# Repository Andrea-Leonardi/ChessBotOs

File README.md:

# ChessBotOs

**End-to-end autonomous physical chess-playing robot** combining a custom 3D-printed **5-bar parallel SCARA manipulator**, **deep-learning computer vision (ResNet-18 + ArUco)**, **Stockfish chess engine**, **distributed ESP32 firmware**, and a **custom 2-layer KiCad mainboard PCB**.

> **Work in Progress:** Core subsystems (3D-printed SCARA hardware, inverse kinematics firmware, ArUco + ResNet-18 vision pipeline, and custom KiCad mainboard PCB) are built and tested; final PCB assembly and full end-to-end game orchestration are currently under active development.

---

## Highlights

- **5-Bar Parallel SCARA Kinematics:** Analytical inverse kinematics (`a = 183 mm`, `b = 230 mm`, `16T:100T` belt reduction) ported from Python (`IK.py`) to real-time ESP32 C++ (`scara_ik.ino`) with trapezoidal acceleration ramps and **~1.6 mm RMS positional accuracy** calibrated across 35 measured board points.
- **2-Stage Computer Vision Pipeline:** Overhead **ESP32-S3 + OV5640** autofocus camera stream with 1:1 hardware crop, **ArUco homography** board warping (`800×800` → 64 cells), and dual **PyTorch ResNet-18** models (3-class occupancy/color + 13-class full piece classification) with Class Activation Map (CAM) interpretability.
- **Custom 2-Layer Mainboard PCB:** Designed from scratch in **KiCad 10.0** (`100 × 100 mm`, **0 DRC errors**, **0 unconnected pads**), integrating an ESP32 38-pin controller, 3× **TMC2209** stepper drivers, triple **MP1584EN** buck rails (5V logic + 6V 25 kg gripper servo + low-profile 10–12V blower fan under ESP32), NC hardware E-Stop cutting motor power only (`VMOT_24V`), 5A fuse, and unified JST-XH connectors.
- **3D-Printed Mechanics & Clock Console:** Full PETG + 2020 aluminum extrusion robot CAD (`ChessBot_checkpoint_4.blend`) and a dedicated touchscreen **Chess Clock Console** (`ChessBot_ClockConsole.blend`) housing an ESP32-S3 4.0" IPS capacitive display and a mechanical MX top switch.

---

## Visual Showcase

<table>
  <tr>
    <td align="center" width="52%">
      
      <br />
      <sub><b>Custom 2-Layer Mainboard PCB v1.3</b> (100×100 mm, KiCad 10.0 — 3× TMC2209, ESP32, 3× MP1584EN, E-Stop)</sub>
    </td>
    <td align="center" width="48%">
      
      <br />
      <sub><b>ResNet-18 Piece Classifier</b> — Conv1 feature maps & Layer4 Class Activation Maps across piece classes</sub>
    </td>
  </tr>
</table>

---

## System Architecture

```mermaid
flowchart LR
    subgraph HOST["Host PC - Python / PyTorch / Stockfish"]
        CV["ArUco Warp + ResNet-18 (3-class & 13-class)"]
        ENG["Stockfish Engine & Game Orchestrator"]
        CV --> ENG
    end

    subgraph CAM["Overhead Vision Node"]
        ESP_CAM["ESP32-S3 + OV5640 (1:1 Square Stream + AF)"]
    end

    subgraph MOTION["Mainboard PCB v1.3 (24V / 12V / 6V / 5V)"]
        ESP_MOT["ESP32 38-pin - 5-Bar SCARA IK + Z-Axis"]
        DRV["3x TMC2209 + NEMA 17 + 25 kg Gripper Servo"]
        ESP_MOT --> DRV
    end

    subgraph HMI["Clock Console (3D Printed)"]
        CLK["ESP32-S3 4.0-inch IPS Touch + MX Button"]
    end

    ESP_CAM -->|HTTP / Wi-Fi| CV
    ENG -->|Move Commands| ESP_MOT
    ENG <-->|Clock & UX State| CLK
```

---

## Repository Structure

```text
ChessBotOs/
├── README.md
├── .gitignore
├── 3Dmodel/                                    # Blender CAD models
│   ├── ChessBot_checkpoint_4.blend             # Full 5-bar SCARA robot assembly (2020 frame + PETG parts)
│   └── ChessBot_ClockConsole.blend             # 3D-printable 4.0" IPS touch clock console + MX switch
├── hardware/
│   └── mainboard_pcb/                          # Custom 2-layer KiCad 10.0 Mainboard v1.3 (100x100 mm)
│       ├── Motherboard_chessbot.kicad_pro
│       ├── Motherboard_chessbot.kicad_sch      # Full schematic (0 ERC errors)
│       ├── Motherboard_chessbot.kicad_pcb      # Routed 2-layer PCB (0 DRC errors, solid B.Cu GND plane)
│       ├── ChessBot_Local.pretty/              # Custom STEP-verified MP1584EN footprint
│       ├── gerbers/                            # Production-ready Gerber + Excellon drill ZIP
│       └── ChessBot_Mainboard_v1.3_PrintCheck_1to1.pdf
├── docs/                                       # Engineering specs, BOM & hardware guides (Italian)
│   ├── riassunto_progetto_chessbot.md          # Complete project & mechatronics overview
│   ├── specifiche_funzionali_chessbot.md       # Functional specs, UX flows & Fair Clock logic
│   ├── bom_componenti_chessbot.md              # Bill of Materials aligned with CAD & PCB
│   ├── guida_pcb_kicad_chessbot.md             # PCB design & assembly guide
│   └── images/                                 # PCB 3D renders
└── test/                                       # Prototype modules & validation tools
    ├── InverseKinematic/
    │   └── IK.py                               # Analytical 5-bar parallel SCARA inverse kinematics
    ├── scara_ik/
    │   └── scara_ik.ino                        # ESP32 C++ IK firmware + serial CLI (a1..h8, z±mm, home)
    ├── stepper/
    │   └── stepper.ino                         # Stepper & microstepping bring-up test
    ├── pinzaInput/                             # Gripper servo actuation test
    ├── esp32_cam_stream/                       # ESP32-S3 (N16R8 + OV5640) web stream + autofocus firmware
    ├── aruco_markers/                          # ArUco marker generator & 800x800 perspective warp
    ├── dataset_tools/                          # Capture, 3/13-class labeling, smart collection & label review
    ├── resnet18/                               # PyTorch ResNet-18 training, live inference & CAM visualizations
    └── stockfish/                              # Stockfish engine integration test
```

---

## Subsystems & Quick Start

### 1. 5-Bar SCARA Kinematics & Motion Control (`test/InverseKinematic`, `test/scara_ik`)
- **Python prototype (`test/InverseKinematic/IK.py`):** Solves left/right shoulder angles `(θ_L, θ_R)` for any `(x, y)` coordinate or chess square (`a1`–`h8`), `home`, and `cemetery` discard zone.
- **ESP32 firmware (`test/scara_ik/scara_ik.ino`):** Real-time coordinated L/R + Z-axis (`T8×8`, `1:3` reduction) motion with trapezoidal velocity ramps and an interactive `115200` baud serial monitor:
  - Squares: `a1` .. `h8` (e.g. `e4`, `a8`)
  - Special targets: `home`, `cemetery`, direct `x,y` coordinates
  - Z-axis: relative `z+10` / `z-10` or absolute `z0` / `z20`
  - Telemetry: `pos` or `?`

### 2. ESP32-S3 Overhead Camera (`test/esp32_cam_stream`)
Firmware for **Goouuu ESP32-S3-N16R8** with **OV5640** sensor:
- Copy `credentials.example.h` → `credentials.h` (git-ignored) and set your Wi-Fi SSID/password. Falls back automatically to the `ESP32S3-CAM` access point (`192.168.4.1`).
- Hardware-cropped **1:1 square resolutions** (`1500×1500`, `1024×1024`, `800×800`) and OV5640 VCM autofocus support (`ESP32_OV5640_AF`).

### 3. ArUco Calibration & Dataset Pipeline (`test/aruco_markers`, `test/dataset_tools`)
Recommended Python environment (`conda activate chess_bot` with `opencv-python`, `numpy`, `torch`, `torchvision`, `pillow`):
```powershell
# 1. Verify ArUco perspective warp (800x800 chessboard grid)
python test/aruco_markers/MakerIdentification.py

# 2. Capture 64 cells (100x100 px) per shot (SPACE to capture, Q to quit)
python test/dataset_tools/DatasetCollector.py

# 3. Label 3-class (occupancy/color) or 13-class (piece types)
python test/dataset_tools/DatasetLabeler.py
python test/dataset_tools/PieceLabeler.py
```
Additional active-learning helpers: `SmartPieceCollector.py` (auto-filters empty squares with the 3-class model), `TargetedPieceCollector.py` (single-piece capture), and `ReviewLabels.py` (error/imbalance auditing).

### 4. ResNet-18 Piece Recognition (`test/resnet18`)
```powershell
# Train on CUDA (3-class and 13-class)
python test/resnet18/train_resnet18.py
python test/resnet18/train_resnet18_pieces.py

# Live camera inference
python test/resnet18/infer_live.py
python test/resnet18/infer_live_pieces.py

# Generate Conv1..Layer4 activation & CAM visualizations
python test/resnet18/visualize_resnet_layers.py
```

### 5. Custom Mainboard PCB (`hardware/mainboard_pcb`)
- **Board:** `100 × 100 mm`, 2 layers, 1 oz Cu, THT + socketed modules (production-ready for JLCPCB / PCBWay).
- **Power rails:** 24V input → 5A fuse (`F1`) → Main Switch (`J18`) → NC E-Stop (`J2`, cuts `VMOT_24V` only so logic stays alive) + triple `MP1584EN` buck converters (`5.0 V` logic/camera/clock, `6.0 V` gripper servo, `10–12 V` low-profile radial blower under ESP32).
- **Manufacturing package:** Ready-to-upload Gerber + Excellon drill archive in [`hardware/mainboard_pcb/gerbers/`](hardware/mainboard_pcb/gerbers/ChessBot_Mainboard_v1.3_PCBWay.zip) and a 1:1 A4 paper fit-check PDF in [`hardware/mainboard_pcb/`](hardware/mainboard_pcb/ChessBot_Mainboard_v1.3_PrintCheck_1to1.pdf).

---

## Project Status & Roadmap

- [x] 3D-printed 5-bar parallel SCARA mechanical design & working physical prototype
- [x] Analytical inverse kinematics (Python & ESP32 C++) calibrated to ~1.6 mm RMS
- [x] ESP32-S3 OV5640 streaming + ArUco homography board extraction
- [x] Custom dataset pipeline + trained 3-class & 13-class ResNet-18 models with CAM visualizations
- [x] Functional specifications, BOM, and 3D-printable 4.0" IPS Clock Console CAD
- [x] Custom 2-layer KiCad 10.0 Mainboard PCB (0 ERC/DRC errors, Gerbers ready for fabrication)
- [ ] PCB assembly & hardware bring-up with TMC2209 silent drivers + endstop homing
- [ ] Unified game orchestrator (`ChessBotOs` host + Stockfish + Fair Clock + auto-setup)
- [ ] ESP32-S3 4.0" LVGL Clock Console UI & Wi-Fi telemetry

---

## Excluded from Git (`.gitignore`)

- `credentials.h` and local secrets
- `datasets/` (raw captured board images and CSV labels)
- `stockfish-windows-x86-64-universal/` (local Stockfish binary > 100 MB)
- KiCad / Blender lockfiles and auto-backups

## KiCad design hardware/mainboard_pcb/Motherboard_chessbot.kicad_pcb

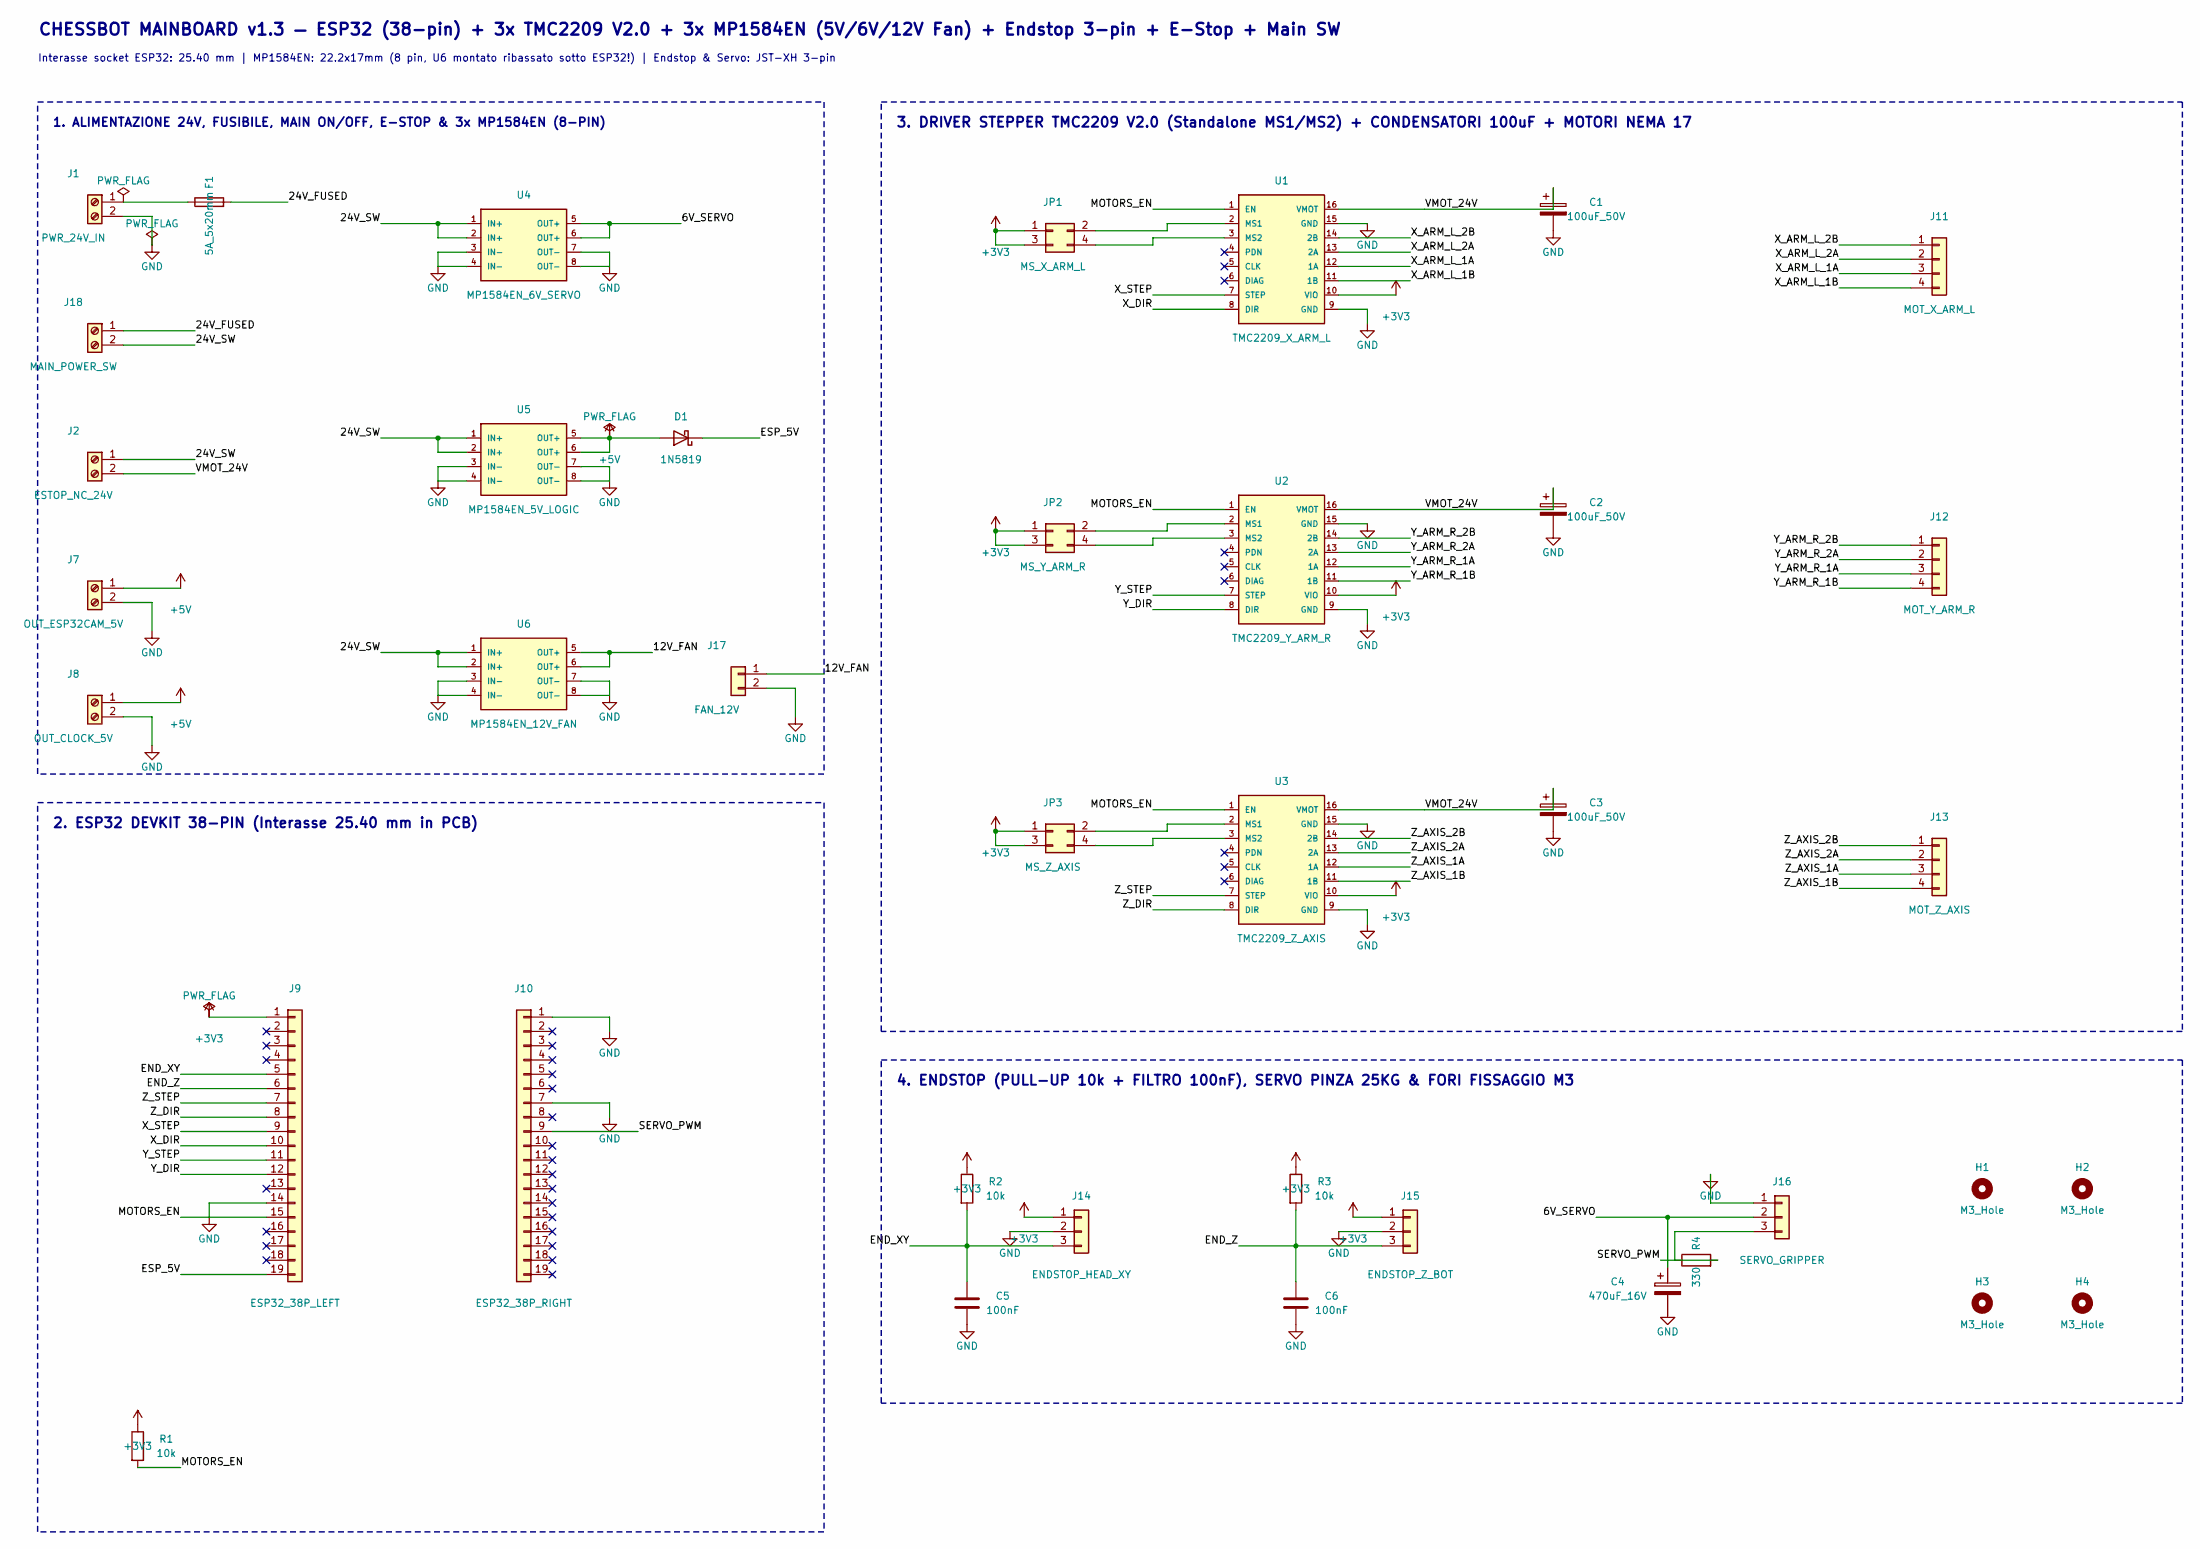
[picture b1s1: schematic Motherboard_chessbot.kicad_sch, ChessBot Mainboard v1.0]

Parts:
C1, C2, C3: 100uF_50V; CP_Radial_D8.0mm_P3.50mm
C4: 470uF_16V; CP_Radial_D8.0mm_P3.50mm
C5, C6: 100nF; C_Disc_D5.0mm_W2.5mm_P5.00mm
D1: 1N5819; D_DO-41_SOD81_P10.16mm_Horizontal
F1: 5A_5x20mm; Fuseholder_Cylinder-5x20mm_Stelvio-Kontek_PTF78_Horizontal_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
H1, H2, H3, H4: M3_Hole; MountingHole_3.2mm_M3
J1: PWR_24V_IN; TerminalBlock_Phoenix_MKDS-1,5-2-5.08_1x02_P5.08mm_Horizont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
J2: ESTOP_NC_24V; TerminalBlock_Phoenix_MKDS-1,5-2-5.08_1x02_P5.08mm_Horizont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
J7: OUT_ESP32CAM_5V; TerminalBlock_Phoenix_MKDS-1,5-2-5.08_1x02_P5.08mm_Horizont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
J8: OUT_CLOCK_5V; TerminalBlock_Phoenix_MKDS-1,5-2-5.08_1x02_P5.08mm_Horizont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
J9: ESP32_38P_LEFT; PinSocket_1x19_P2.54mm_Vertical
J10: ESP32_38P_RIGHT; PinSocket_1x19_P2.54mm_Vertical
J11: MOT_X_ARM_L; JST_XH_B4B-XH-A_1x04_P2.50mm_Vertical
J12: MOT_Y_ARM_R; JST_XH_B4B-XH-A_1x04_P2.50mm_Vertical
J13: MOT_Z_AXIS; JST_XH_B4B-XH-A_1x04_P2.50mm_Vertical
J14: ENDSTOP_HEAD_XY; JST_XH_B3B-XH-A_1x03_P2.50mm_Vertical
J15: ENDSTOP_Z_BOT; JST_XH_B3B-XH-A_1x03_P2.50mm_Vertical
J16: SERVO_GRIPPER; JST_XH_B3B-XH-A_1x03_P2.50mm_Vertical
J17: FAN_12V; JST_XH_B2B-XH-A_1x02_P2.50mm_Vertical
J18: MAIN_POWER_SW; TerminalBlock_Phoenix_MKDS-1,5-2-5.08_1x02_P5.08mm_Horizont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
JP1: MS_X_ARM_L; PinHeader_2x02_P2.54mm_Vertical
JP2: MS_Y_ARM_R; PinHeader_2x02_P2.54mm_Vertical
JP3: MS_Z_AXIS; PinHeader_2x02_P2.54mm_Vertical
R1, R2, R3: 10k; R_Axial_DIN0207_L6.3mm_D2.5mm_P10.16mm_Horizontal
R4: 330; R_Axial_DIN0207_L6.3mm_D2.5mm_P10.16mm_Horizontal
U1: TMC2209_X_ARM_L; Pololu_Breakout-16_15.2x20.3mm
U2: TMC2209_Y_ARM_R; Pololu_Breakout-16_15.2x20.3mm
U3: TMC2209_Z_AXIS; Pololu_Breakout-16_15.2x20.3mm
U4: MP1584EN_6V_SERVO; MP1584EN_22.2x17mm
U5: MP1584EN_5V_LOGIC; MP1584EN_22.2x17mm
U6: MP1584EN_12V_FAN; MP1584EN_22.2x17mm

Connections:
+3V3: J9.1, J14.1, J15.1, JP1.1, JP1.3, JP2.1, JP2.3, JP3.1, JP3.3, R1.1, R2.1, R3.1, U1.10 (VIO), U2.10 (VIO), U3.10 (VIO)
+5V: D1.2 (A), J7.1, J8.1, U5.5 (OUT+), U5.6 (OUT+)
/6V_SERVO: C4.1, J16.2, U4.5 (OUT+), U4.6 (OUT+)
/12V_FAN: J17.1, U6.5 (OUT+), U6.6 (OUT+)
/24V_FUSED: F1.2, J18.1
/24V_SW: J2.1, J18.2, U4.1 (IN+), U4.2 (IN+), U5.1 (IN+), U5.2 (IN+), U6.1 (IN+), U6.2 (IN+)
/END_XY: C5.1, J9.5, J14.3, R2.2
/END_Z: C6.1, J9.6, J15.3, R3.2
/ESP_5V: D1.1 (K), J9.19
/SERVO_PWM: J10.9, R4.2
/VMOT_24V: C1.1, C2.1, C3.1, J2.2, U1.16 (VMOT), U2.16 (VMOT), U3.16 (VMOT)
/X_ARM_L_1A: J11.3, U1.12 (1A)
/X_ARM_L_1B: J11.4, U1.11 (1B)
/X_ARM_L_2A: J11.2, U1.13 (2A)
/X_ARM_L_2B: J11.1, U1.14 (2B)
/X_DIR: J9.10, U1.8 (DIR)
/X_STEP: J9.9, U1.7 (STEP)
/Y_ARM_R_1A: J12.3, U2.12 (1A)
/Y_ARM_R_1B: J12.4, U2.11 (1B)
/Y_ARM_R_2A: J12.2, U2.13 (2A)
/Y_ARM_R_2B: J12.1, U2.14 (2B)
/Y_DIR: J9.12, U2.8 (DIR)
/Y_STEP: J9.11, U2.7 (STEP)
/Z_AXIS_1A: J13.3, U3.12 (1A)
/Z_AXIS_1B: J13.4, U3.11 (1B)
/Z_AXIS_2A: J13.2, U3.13 (2A)
/Z_AXIS_2B: J13.1, U3.14 (2B)
/Z_DIR: J9.8, U3.8 (DIR)
/Z_STEP: J9.7, U3.7 (STEP)
unnamed: F1.1, J1.1
unnamed: J16.3, R4.1
unnamed: JP1.2, U1.2 (MS1)
unnamed: JP1.4, U1.3 (MS2)
unnamed: JP2.2, U2.2 (MS1)
unnamed: JP2.4, U2.3 (MS2)
unnamed: JP3.2, U3.2 (MS1)
unnamed: JP3.4, U3.3 (MS2)

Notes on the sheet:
CHESSBOT MAINBOARD v1.3 — ESP32 (38-pin) + 3x TMC2209 V2.0 + 3x MP1584EN (5V/6V/12V Fan) + Endstop 3-pin + E-Stop + Main SW
Interasse socket ESP32: 25.40 mm | MP1584EN: 22.2x17mm (8 pin, U6 montato ribassato sotto ESP32!) | Endstop & Servo: JST-XH 3-pin
1. ALIMENTAZIONE 24V, FUSIBILE, MAIN ON/OFF, E-STOP & 3x MP1584EN (8-PIN)
2. ESP32 DEVKIT 38-PIN (Interasse 25.40 mm in PCB)
3. DRIVER STEPPER TMC2209 V2.0 (Standalone MS1/MS2) + CONDENSATORI 100uF + MOTORI NEMA 17
4. ENDSTOP (PULL-UP 10k + FILTRO 100nF), SERVO PINZA 25KG & FORI FISSAGGIO M3

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
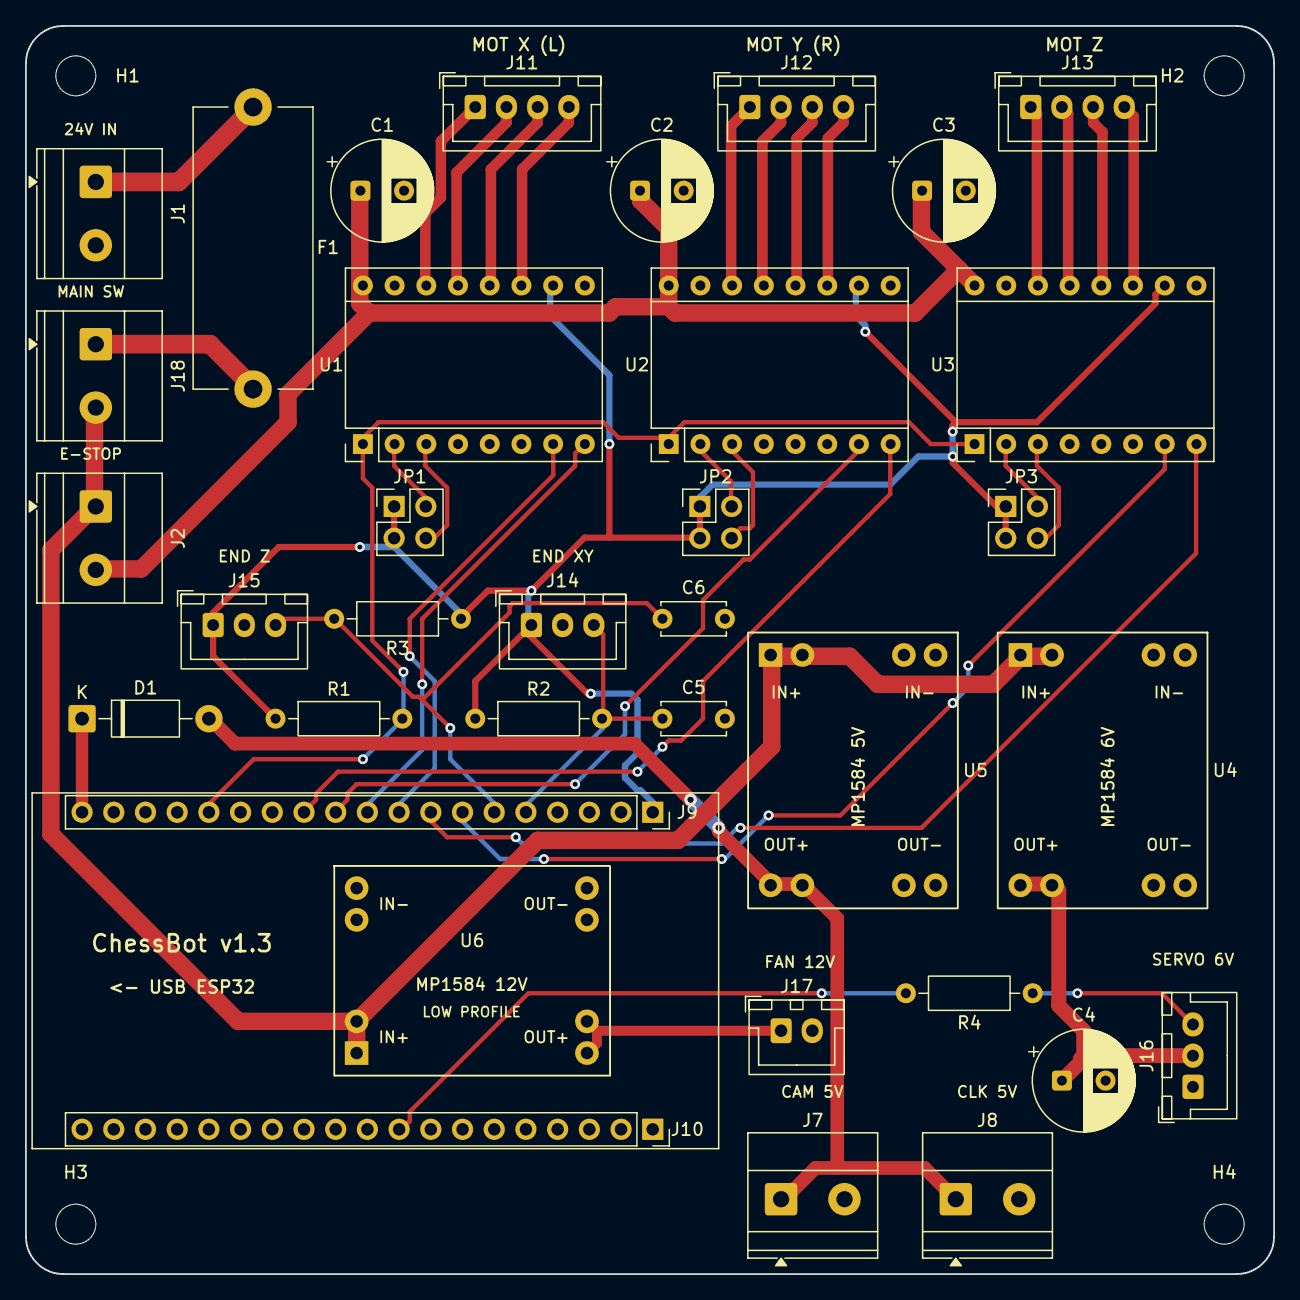
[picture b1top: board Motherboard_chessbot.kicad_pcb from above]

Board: 2 copper layers, 100.0 x 100.0 mm, 39 parts (0 on the bottom side), 39 nets.
